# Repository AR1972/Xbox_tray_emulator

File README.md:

# Original Xbox DVD tray emulator

# BOM
C1,C2 - 1uf 10v - 805

J1 - Hirose_DF11-14DP-2DSA not used for QSB

R1 - 10k - 805

U1 - ATTINY13A-SF or narrow ATTINY13A-SS7R - SOIC-8

U2 - AP2127N-3.3 - SOT-23

# PCB ordering info

Layers: 2

Thickness: 1.2mm

Material: FR-4: TG150

Min track/spacing: 6/6mil

Min hole size: 0.3mm

Surface finish: HASL with lead

Via process: Tenting vias

Finished copper: 1 oz Cu

# QSB ordering info

Layers: 2

Thickness: 0.6mm

Material: FR-4: TG150

Min track/spacing: 6/6mil

Min hole size: 0.3mm

Surface finish: HASL with lead

Via process: Tenting vias

Finished copper: 1 oz Cu

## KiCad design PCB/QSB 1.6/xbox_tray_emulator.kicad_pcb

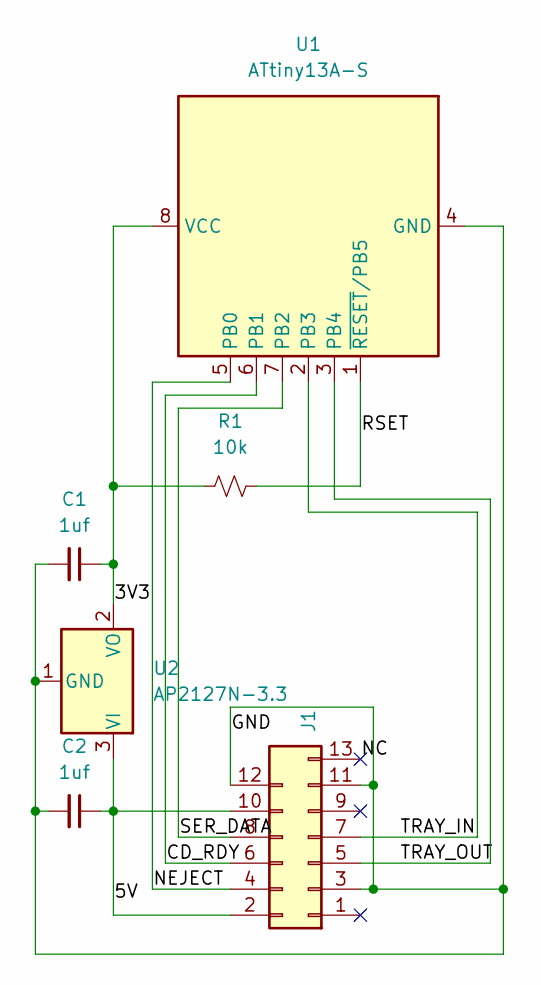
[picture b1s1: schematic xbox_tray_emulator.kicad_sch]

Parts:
C1, C2: 1uf; C_0805_2012Metric_Pad1.18x1.45mm_HandSolder
J1: to Xbox; Hirose_DF11-14DP-2DSA_2x07_P2.00mm_Vertical
R1: 10k; R_0805_2012Metric_Pad1.20x1.40mm_HandSolder
U1: ATtiny13A-S; SOIC-8W_5.3x5.3mm_P1.27mm
U2: AP2127N-3.3; SOT-23

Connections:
/3V3: C1.1, R1.1, U1.8 (VCC), U2.2 (VO)
/5V: C2.1, J1.2, J1.10, U2.3 (VI)
/CD_RDY: J1.6, U1.6 (PB1)
/GND: C1.2, C2.2, J1.3, J1.11, J1.12, U1.4 (GND), U2.1 (GND)
/NC: J1.13
/NEJECT: J1.4, U1.5 (PB0)
/RSET: R1.2, U1.1 (~RESET/PB5)
/SER_DATA: J1.8, U1.7 (PB2)
/TRAY_IN: J1.7, U1.2 (PB3)
/TRAY_OUT: J1.5, U1.3 (PB4)

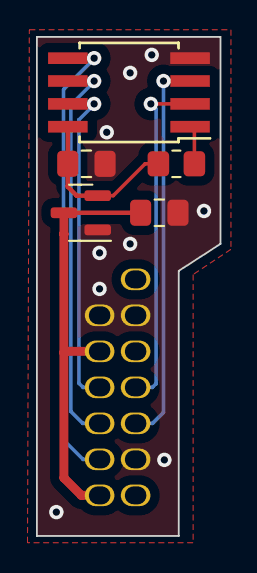
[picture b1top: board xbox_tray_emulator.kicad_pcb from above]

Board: 2 copper layers, 10.2 x 27.7 mm, 6 parts (1 on the bottom side), 9 nets.

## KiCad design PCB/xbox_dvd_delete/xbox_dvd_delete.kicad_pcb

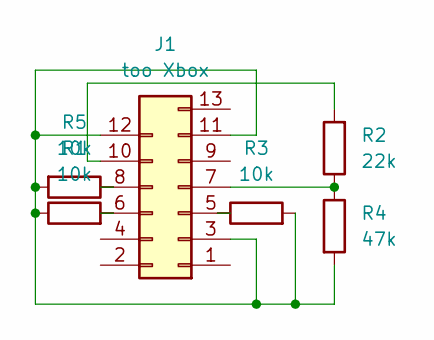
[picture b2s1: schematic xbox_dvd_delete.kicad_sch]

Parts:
J1: too Xbox; Hirose_DF11-14DP-2DSA_2x07_P2.00mm_Vertical
R1, R3, R5: 10k; R_0603_1608Metric_Pad0.98x0.95mm_HandSolder
R2: 22k; R_0603_1608Metric_Pad0.98x0.95mm_HandSolder
R4: 47k; R_0603_1608Metric_Pad0.98x0.95mm_HandSolder

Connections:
unnamed: J1.5, R3.1
unnamed: J1.6, R1.2
unnamed: J1.7, R2.1, R4.1
unnamed: J1.8, R5.1
unnamed: J1.10, R2.2
unnamed: J1.3, J1.11, J1.12, R1.1, R3.2, R4.2, R5.2

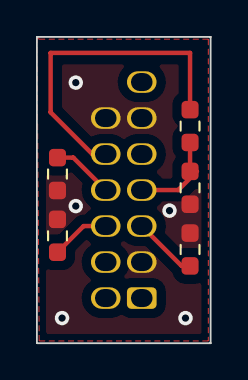
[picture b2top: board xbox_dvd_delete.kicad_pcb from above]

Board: 2 copper layers, 9.7 x 17.0 mm, 6 parts (1 on the bottom side), 6 nets.

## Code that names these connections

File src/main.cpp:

/*
	   DO WHAT THE FUCK YOU WANT TO PUBLIC LICENSE
					Version 2, December 2004

 Copyright (C) 2004 Sam Hocevar <sam@hocevar.net>

 Everyone is permitted to copy and distribute verbatim or modified
 copies of this license document, and changing it is allowed as long
 as the name is changed.

			DO WHAT THE FUCK YOU WANT TO PUBLIC LICENSE
   TERMS AND CONDITIONS FOR COPYING, DISTRIBUTION AND MODIFICATION

  0. You just DO WHAT THE FUCK YOU WANT TO.
*/

#include <Arduino.h>
#include <avr/sleep.h>
#include <avr/interrupt.h>
#include <avr/power.h>

#define CLOSED 1
#define OPEN 0
#define NEJECT_PIN PB0
#define CD_RDY_PIN PB1
#define SER_DATA_PIN PB2
#define TRAY_IN_PIN PB3
#define TRAY_OUT_PIN PB4

volatile bool tray_status = CLOSED;

void setup()
{
	// disable intrrupts
	cli();
	// ADC off
	ADCSRA &= ~_BV(ADEN);
	// setup pin 5 as our interrupt pin
	GIMSK |= _BV(PCIE);
	PCMSK |= _BV(NEJECT_PIN);
	pinMode(NEJECT_PIN, INPUT);
	// setup output
	pinMode(TRAY_OUT_PIN, OUTPUT);
	pinMode(TRAY_IN_PIN, OUTPUT);
	pinMode(SER_DATA_PIN, OUTPUT);
	pinMode(CD_RDY_PIN, OUTPUT);
	// setup as tray closed no disc in drive
	digitalWrite(TRAY_OUT_PIN, LOW);
	digitalWrite(TRAY_IN_PIN, HIGH);
	digitalWrite(CD_RDY_PIN, LOW);
	// terminate SER_DATA to avoid possible issues
	digitalWrite(SER_DATA_PIN, LOW);
	// enable interrupts
	sei();
}

void sleep()
{
	ACSR = ADMUX = ADCSRA = 0;
	// Analog comparator off
	ACSR |= _BV(ACD);
	// switch Analog to Digitalconverter off
	ADCSRA &= ~_BV(ADEN);
	set_sleep_mode(SLEEP_MODE_PWR_DOWN);
	power_all_disable();
	sleep_enable();
	cli();
	// Disable BOD, step 1
	BODCR = _BV(BODSE) | _BV(BODS);
	// Second step
	BODCR = _BV(BODS);
	sei();
	sleep_cpu();
	sleep_disable();
	power_all_enable();
}

ISR(PCINT0_vect)
{
	GIMSK &= ~_BV(PCIE);
	// NEJECT pin is normaly high only respond when pin changes to low
	if (!digitalRead(NEJECT_PIN))
	{
		if (tray_status == CLOSED)
		{
			// if tray is closed emulate the tray opening
			digitalWrite(CD_RDY_PIN, HIGH);
			digitalWrite(TRAY_IN_PIN, LOW);
			delay(1000);
			digitalWrite(TRAY_OUT_PIN, HIGH);
			delay(1000);
			digitalWrite(CD_RDY_PIN, LOW);
			tray_status = OPEN;
		}
		else
		{
			// if tray is open emulate the tray closing
			digitalWrite(CD_RDY_PIN, LOW);
			digitalWrite(TRAY_IN_PIN, HIGH);
			delay(1000);
			digitalWrite(TRAY_OUT_PIN, LOW);
			digitalWrite(TRAY_IN_PIN, LOW);
			delay(2000);
			digitalWrite(TRAY_IN_PIN, HIGH);
			tray_status = CLOSED;
		}
	}
	GIMSK |= _BV(PCIE);
}

void loop()
{
	// power down the cpu when not servicing an interrupt
	sleep();
}

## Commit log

2023-10-30 First!!!
2023-10-30 add README.md
2023-11-04 modify for ATtiny13A
2023-11-04 upload firmwar to socketed ATtiny13a via USBTINY
2023-11-04 set CPU frequency, correct delay
2023-11-05 add PCB
2023-11-05 PCB cleanup
2023-11-06 rename PCB directory, turn off ADC
2023-11-06 reduce sleep current from 200uA to 50uA
2023-11-07 Xbox DVD logic levels are 3.3v, a 3.3v regulator was added to the PCB so the ATtiny13a will output and accept 3.3v logic. ATtiny13a sleep current draw is now a fration of a uA. modify tray open seque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
2023-11-09 add ground fill
2023-11-12 add psudo-QSB
2023-11-14 clean up
2023-11-15 shrink PCB a little
2023-11-21 correct pin signaling
2023-11-21 adjust pin timings, add logic analyzer images
2023-11-22 disable pin change interrupts while in ISR
2023-11-22 add passive dvd delete board
2023-11-25 increase U1 pads for "narrow" ATtiny13
2024-03-05 add BOM and PCB/QSB ordering info
2024-03-05 Update README.md
    fix formating
2025-10-12 fix fitment for 1.6 revision Xbox
2025-10-15 add net lables, add firmware, update .gitignore
2025-10-15 adjust componets locations to make DRC happy, add gerbers.
